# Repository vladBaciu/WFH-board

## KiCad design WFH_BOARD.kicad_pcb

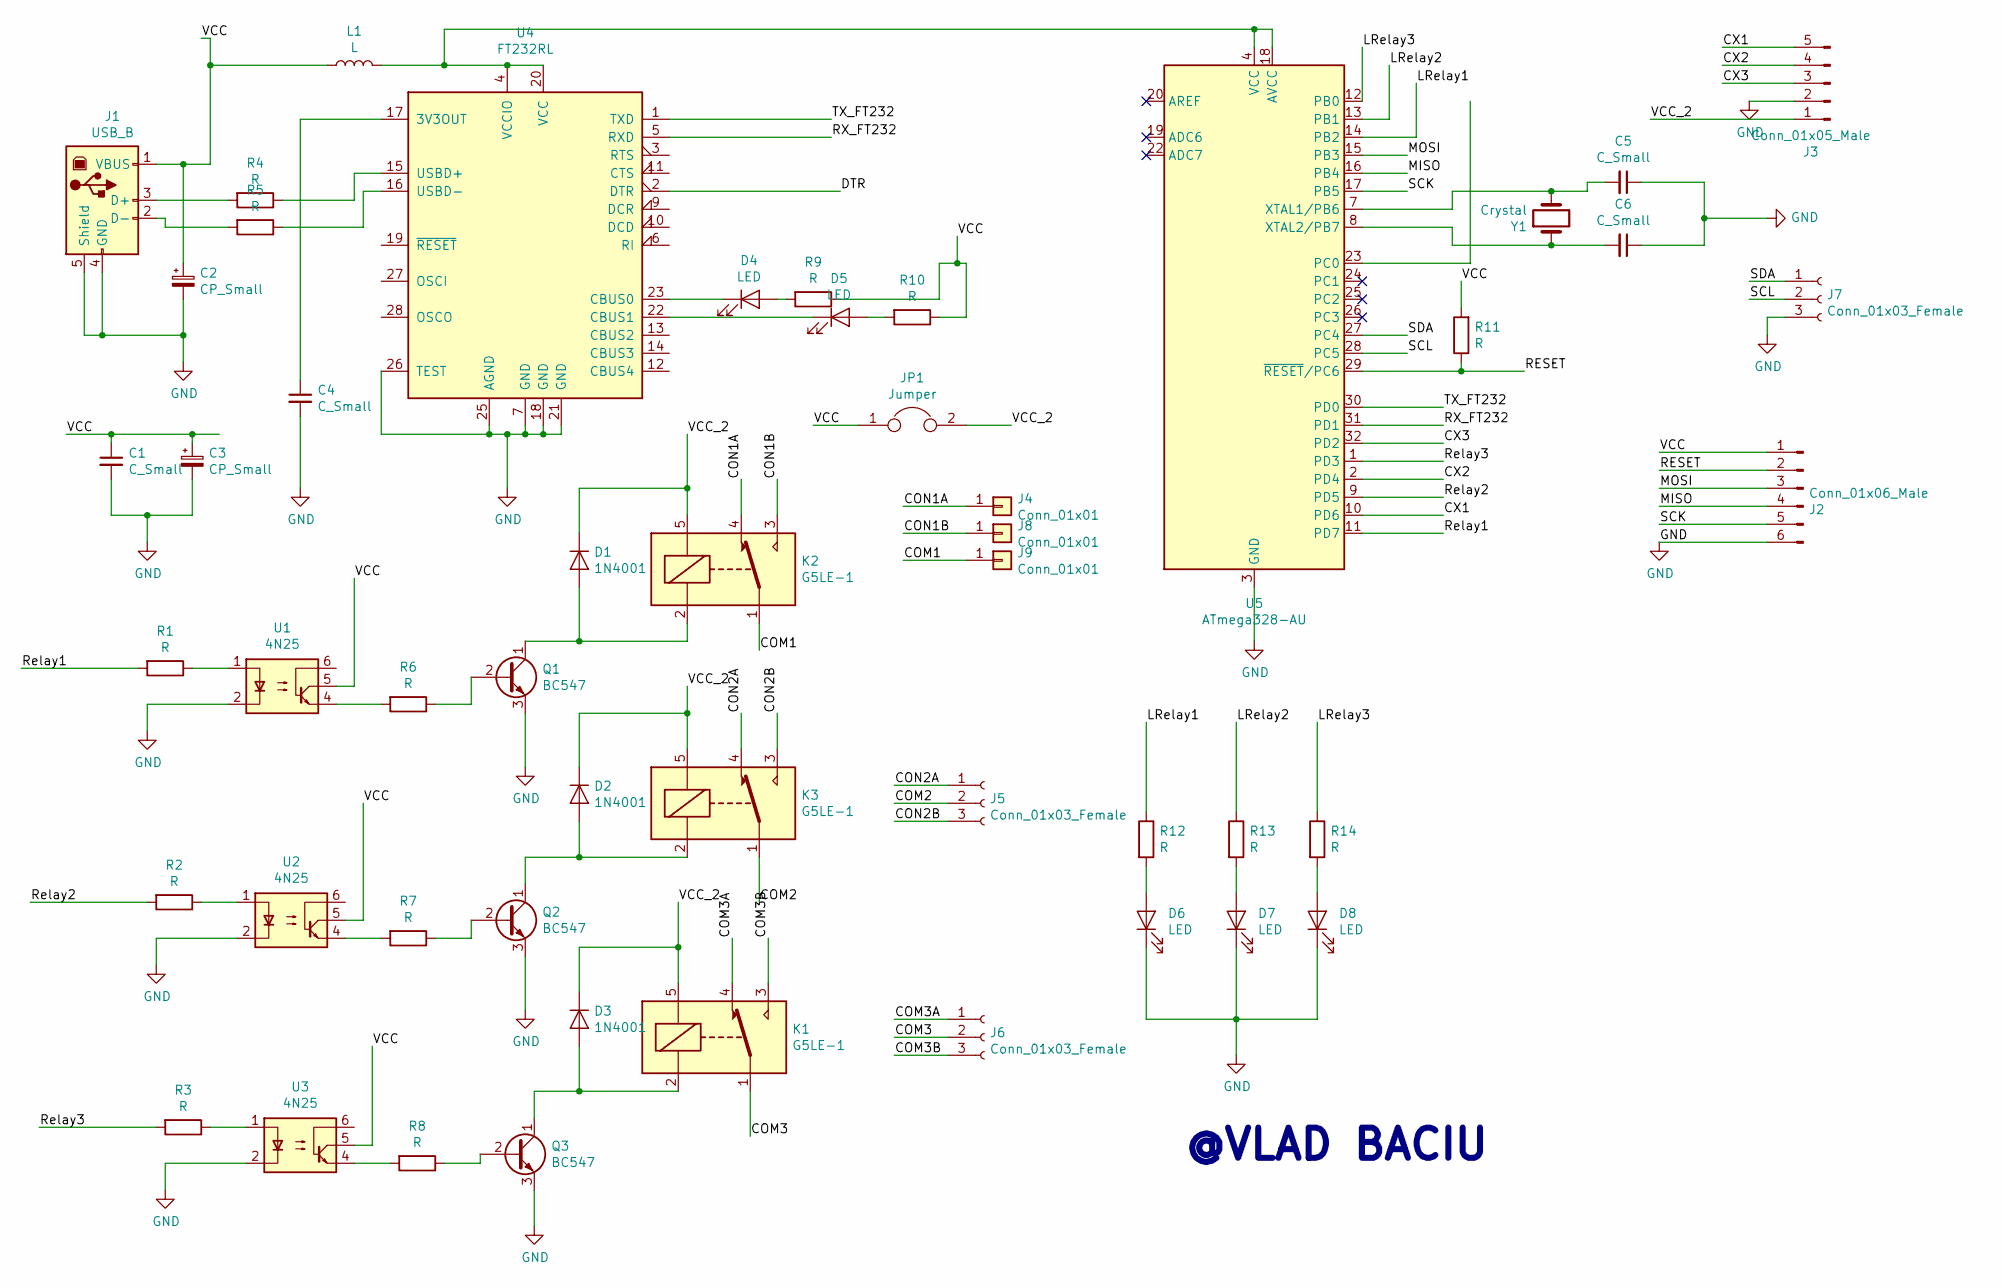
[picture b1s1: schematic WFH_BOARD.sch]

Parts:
C1, C4: C_Small; C_1206_3216Metric_Pad1.42x1.75mm_HandSolder
C2, C3: CP_Small; C_Elec_10x10.2
C5, C6: C_Small; C_1210_3225Metric_Pad1.42x2.65mm_HandSolder
D1, D2, D3: 1N4001; D_DO-41_SOD81_P10.16mm_Horizontal
D4, D5, D6, D7, D8: LED; LED_1206_3216Metric_Pad1.42x1.75mm_HandSolder
J1: USB_B; USB_B_OST_USB-B1HSxx_Horizontal
J2: Conn_01x06_Male; PinHeader_2x03_P2.54mm_Vertical
J3: Conn_01x05_Male; PinHeader_1x05_P2.54mm_Vertical
J4, J8, J9: Conn_01x01; SolderJumper-3_P2.0mm_Open_TrianglePad1.0x1.5mm
J5, J6: Conn_01x03_Female; PhoenixContact_MSTBVA_2,5_3-G-5,08_1x03_P5.08mm_Vertical
J7: Conn_01x03_Female; PinHeader_1x03_P2.54mm_Vertical
JP1: Jumper; PinHeader_1x02_P2.54mm_Vertical
K1, K2, K3: G5LE-1; Relay_SPDT_Omron-G5LE-1
L1: L; L_1206_3216Metric_Pad1.42x1.75mm_HandSolder
Q1, Q2, Q3: BC547; TO-92_Inline
R1, R2, R3, R4, R5, R6, R7, R8, R9, R10, R11, R12, R13, R14: R; R_1206_3216Metric_Pad1.42x1.75mm_HandSolder
U1, U2, U3: 4N25; DIP-6_W7.62mm
U4: FT232RL; SSOP-28_5.3x10.2mm_P0.65mm
U5: ATmega328-AU; TQFP-32_7x7mm_P0.8mm
Y1: Crystal; Resonator-2Pin_W7.0mm_H2.5mm

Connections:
/COM1: J9.1, J9.2, J9.3, K2.1
/COM2: J5.2, K3.1
/COM3: J6.2, K1.1
/COM3A: J6.1, K1.4
/COM3B: J6.3, K1.3
/CON1A: J4.1, J4.2, J4.3, K2.4
/CON1B: J8.1, J8.2, J8.3, K2.3
/CON2A: J5.1, K3.4
/CON2B: J5.3, K3.3
/CX1: J3.5, U5.10 (PD6)
/CX2: J3.4, U5.2 (PD4)
/CX3: J3.3, U5.32 (PD2)
/DTR: U4.2 (DTR)
/LRelay1: R12.1, U5.14 (PB2)
/LRelay2: R13.1, U5.13 (PB1)
/LRelay3: R14.1, U5.12 (PB0)
/MISO: J2.4, U5.16 (PB4)
/MOSI: J2.3, U5.15 (PB3)
/RESET: J2.2, R11.1, U5.29 (~RESET~/PC6)
/RX_FT232: U4.5 (RXD), U5.31 (PD1)
/Relay1: R1.2, U5.11 (PD7)
/Relay2: R2.2, U5.9 (PD5)
/Relay3: R3.2, U5.1 (PD3)
/SCK: J2.5, U5.17 (PB5)
/SCL: J7.2, U5.28 (PC5)
/SDA: J7.1, U5.27 (PC4)
/TX_FT232: U4.1 (TXD), U5.30 (PD0)
/VCC: C1.1, C2.1, C3.1, J1.1 (VBUS), J2.1, JP1.1, L1.1, R9.1, R10.1, R11.2, U1.5, U2.5, U3.5
/VCC_2: D1.1 (K), D2.1 (K), D3.1 (K), J3.1, JP1.2, K1.5, K2.5, K3.5
GND: C1.2, C2.2, C3.2, C4.2, C5.1, C6.1, D6.1 (K), D7.1 (K), D8.1 (K), J1.4 (GND), J1.5 (Shield), J2.6, J3.2, J7.3, Q1.3 (E), Q2.3 (E), Q3.3 (E), U1.2, U2.2, U3.2, U4.7 (GND), U4.18 (GND), U4.21 (GND), U4.25 (AGND), U4.26 (TEST), U5.3 (GND), U5.5 (GND), U5.21 (GND)
unnamed: C4.1, U4.17 (3V3OUT)
unnamed: C5.2, U5.7 (XTAL1/PB6), Y1.2
unnamed: C6.2, U5.8 (XTAL2/PB7), Y1.1
unnamed: D1.2 (A), K2.2, Q1.1 (C)
unnamed: D2.2 (A), K3.2, Q2.1 (C)
unnamed: D3.2 (A), K1.2, Q3.1 (C)
unnamed: D4.1 (K), U4.23 (CBUS0)
unnamed: D4.2 (A), R9.2
unnamed: D5.1 (K), U4.22 (CBUS1)
unnamed: D5.2 (A), R10.2
unnamed: D6.2 (A), R12.2
unnamed: D7.2 (A), R13.2
unnamed: D8.2 (A), R14.2
unnamed: J1.2 (D-), R5.2
unnamed: J1.3 (D+), R4.2
unnamed: L1.2, U4.4 (VCCIO), U4.20 (VCC), U5.4 (VCC), U5.6 (VCC), U5.18 (AVCC)
unnamed: Q1.2 (B), R6.1
unnamed: Q2.2 (B), R7.1
unnamed: Q3.2 (B), R8.1
unnamed: R1.1, U1.1
unnamed: R2.1, U2.1
unnamed: R3.1, U3.1
unnamed: R4.1, U4.15 (USBD+)
unnamed: R5.1, U4.16 (USBD-)
unnamed: R6.2, U1.4
unnamed: R7.2, U2.4
unnamed: R8.2, U3.4

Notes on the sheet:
@VLAD BACIU

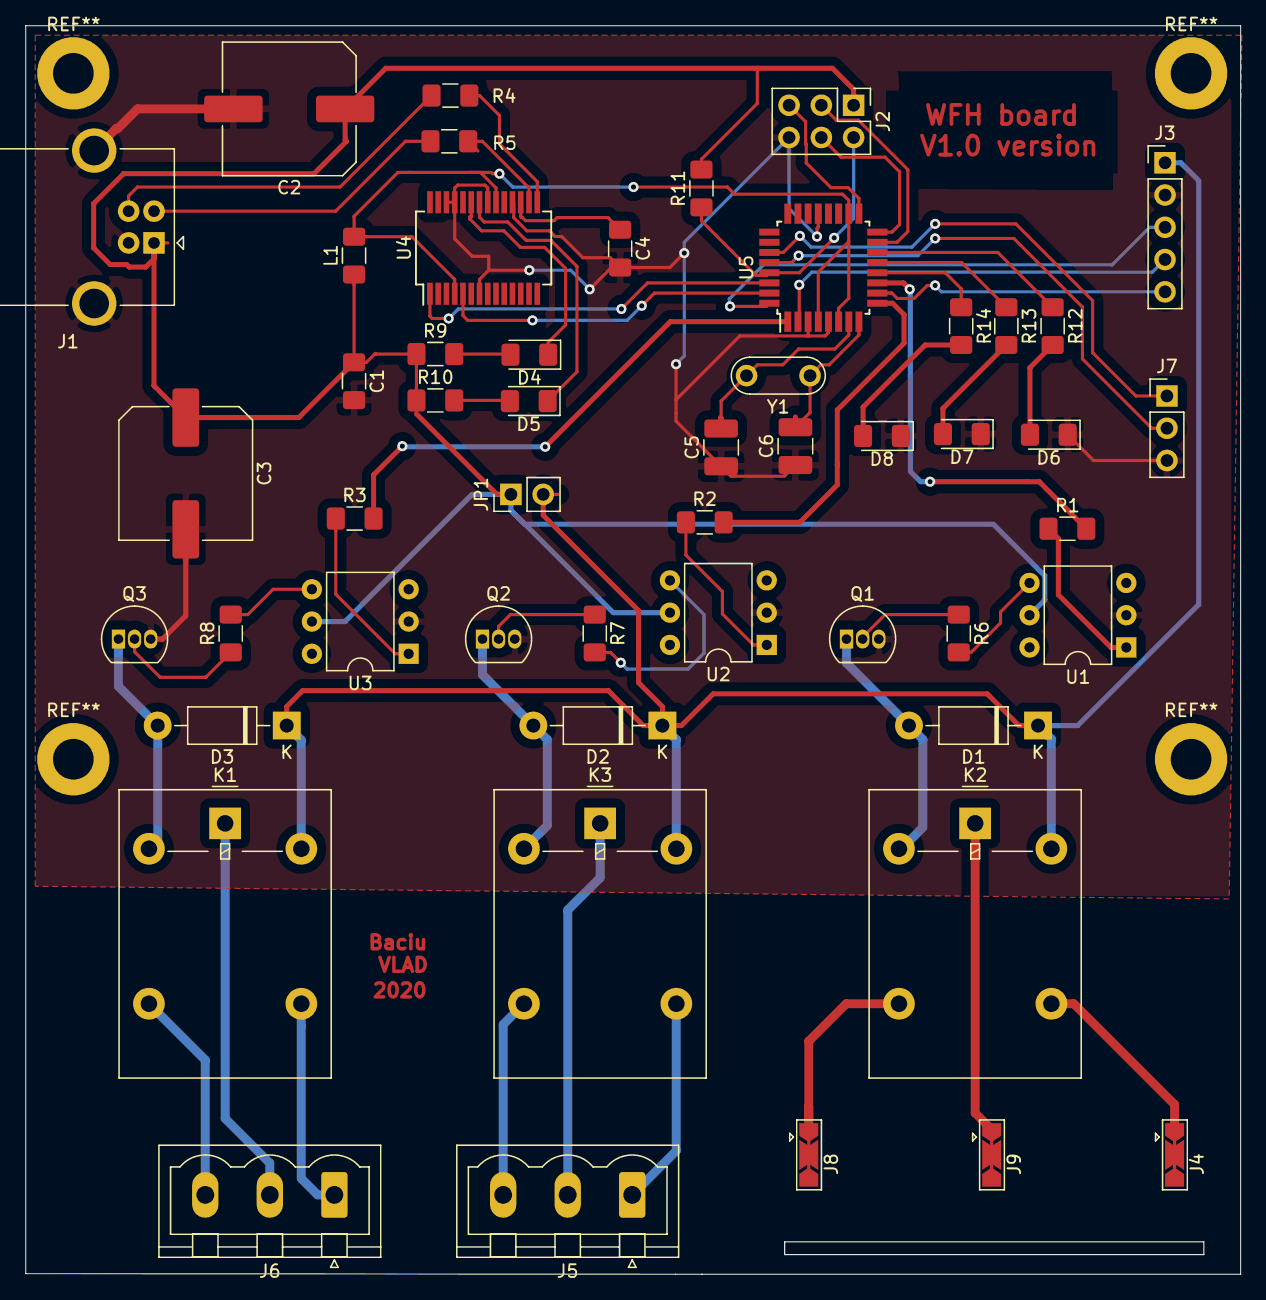
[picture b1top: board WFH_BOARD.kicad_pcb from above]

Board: 2 copper layers, 95.7 x 98.3 mm, 51 parts (0 on the bottom side), 56 nets.

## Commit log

2020-04-08 Final modifications
